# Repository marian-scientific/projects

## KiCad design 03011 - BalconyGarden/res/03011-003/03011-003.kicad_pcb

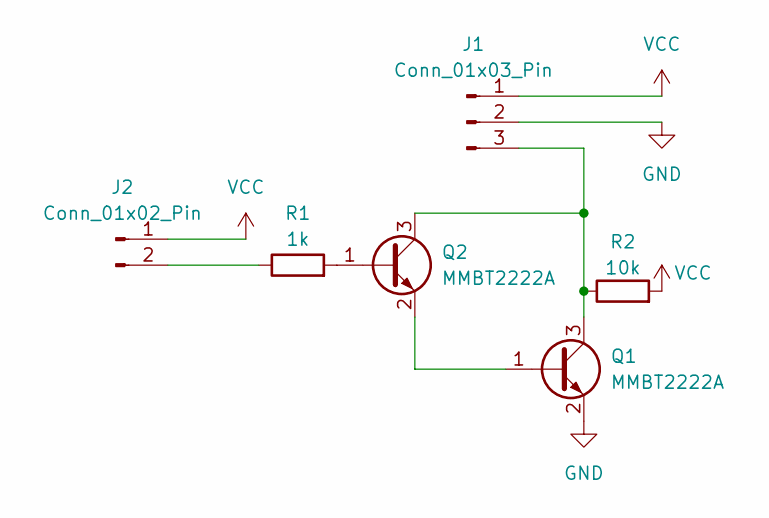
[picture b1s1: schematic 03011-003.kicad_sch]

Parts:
J1: Conn_01x03_Pin; PinHeader_1x03_P2.54mm_Vertical
J2: Conn_01x02_Pin; PinHeader_1x02_P2.54mm_Vertical
Q1, Q2: MMBT2222A; SOT-23
R1: 1k; R_1206_3216Metric
R2: 10k; R_1206_3216Metric

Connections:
GND: J1.2, Q1.2 (E)
unnamed: J1.3, Q1.3 (C), Q2.3 (C), R2.1
unnamed: J2.2, R1.1
unnamed: Q1.1 (B), Q2.2 (E)
unnamed: Q2.1 (B), R1.2
VCC: J1.1, J2.1, R2.2

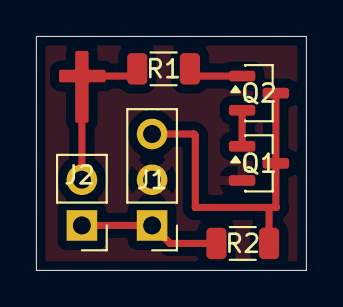
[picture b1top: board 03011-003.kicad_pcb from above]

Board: 2 copper layers, 15.0 x 13.0 mm, 6 parts (0 on the bottom side), 6 nets.

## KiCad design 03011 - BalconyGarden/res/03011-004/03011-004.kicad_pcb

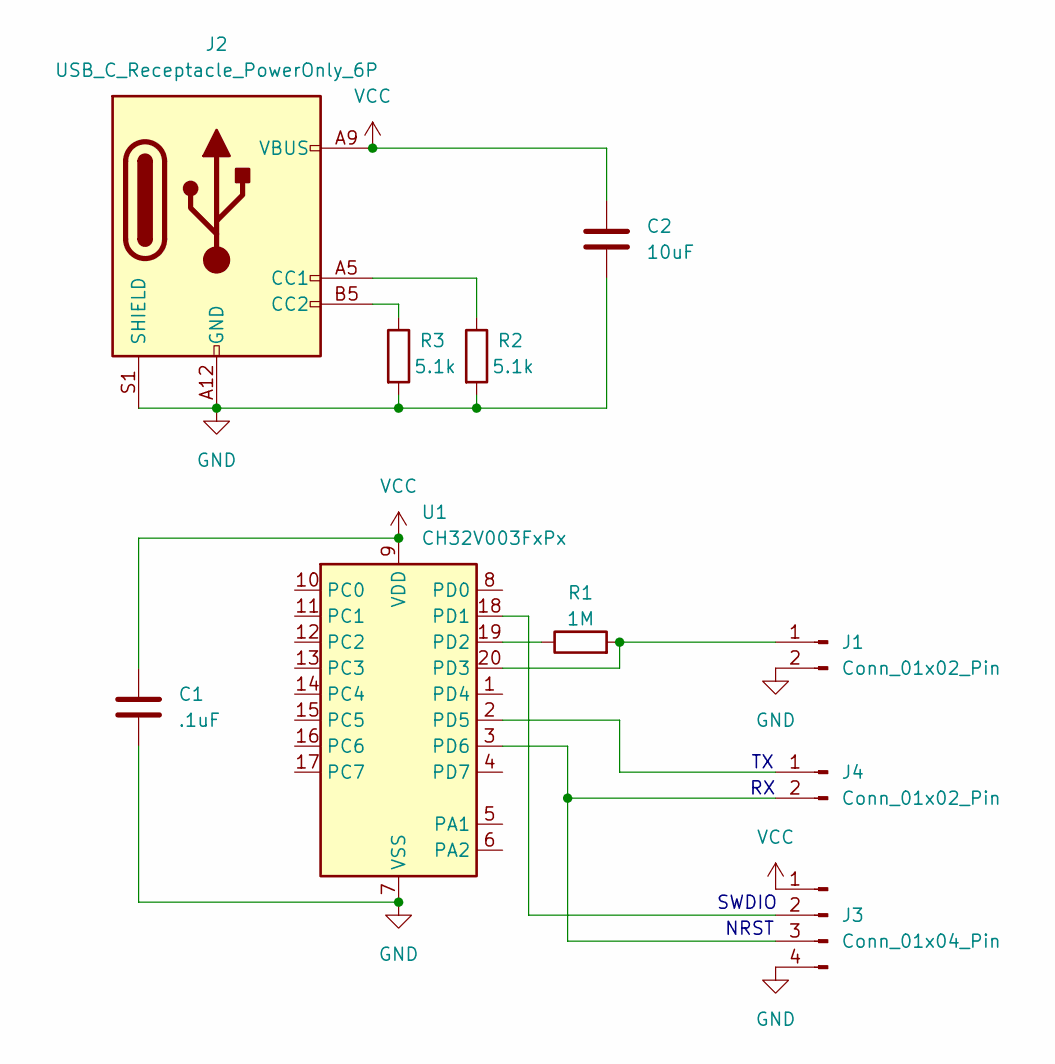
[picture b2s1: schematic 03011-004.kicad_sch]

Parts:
C1: .1uF; C_1206_3216Metric
C2: 10uF; C_1206_3216Metric
J1, J4: Conn_01x02_Pin; PinHeader_1x02_P2.54mm_Vertical
J2: USB_C_Receptacle_PowerOnly_6P; USB_C_Receptacle_GCT_USB4125-xx-x_6P_TopMnt_Horizontal
J3: Conn_01x04_Pin; PinHeader_1x04_P2.54mm_Vertical
R1: 1M; R_1206_3216Metric
R2, R3: 5.1k; R_1206_3216Metric
U1: CH32V003FxPx; TSSOP-20_4.4x6.5mm_P0.65mm

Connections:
GND: C1.2, C2.2, J1.2, J2.A12 (GND), J2.B12 (GND), J2.S1 (SHIELD), J3.4, R2.2, R3.2, U1.7 (VSS)
unnamed: J1.1, R1.2, U1.20 (PD3)
unnamed: J2.A5 (CC1), R2.1
unnamed: J2.B5 (CC2), R3.1
unnamed: J3.2, U1.18 (PD1)
unnamed: J3.3, J4.2, U1.3 (PD6)
unnamed: J4.1, U1.2 (PD5)
unnamed: R1.1, U1.19 (PD2)
VCC: C1.1, C2.1, J2.A9 (VBUS), J2.B9 (VBUS), J3.1, U1.9 (VDD)

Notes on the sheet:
SWDIO
NRST

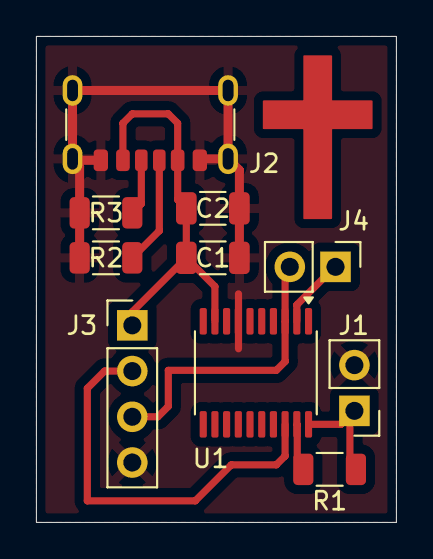
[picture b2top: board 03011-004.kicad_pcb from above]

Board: 2 copper layers, 20.0 x 27.0 mm, 10 parts (0 on the bottom side), 9 nets.

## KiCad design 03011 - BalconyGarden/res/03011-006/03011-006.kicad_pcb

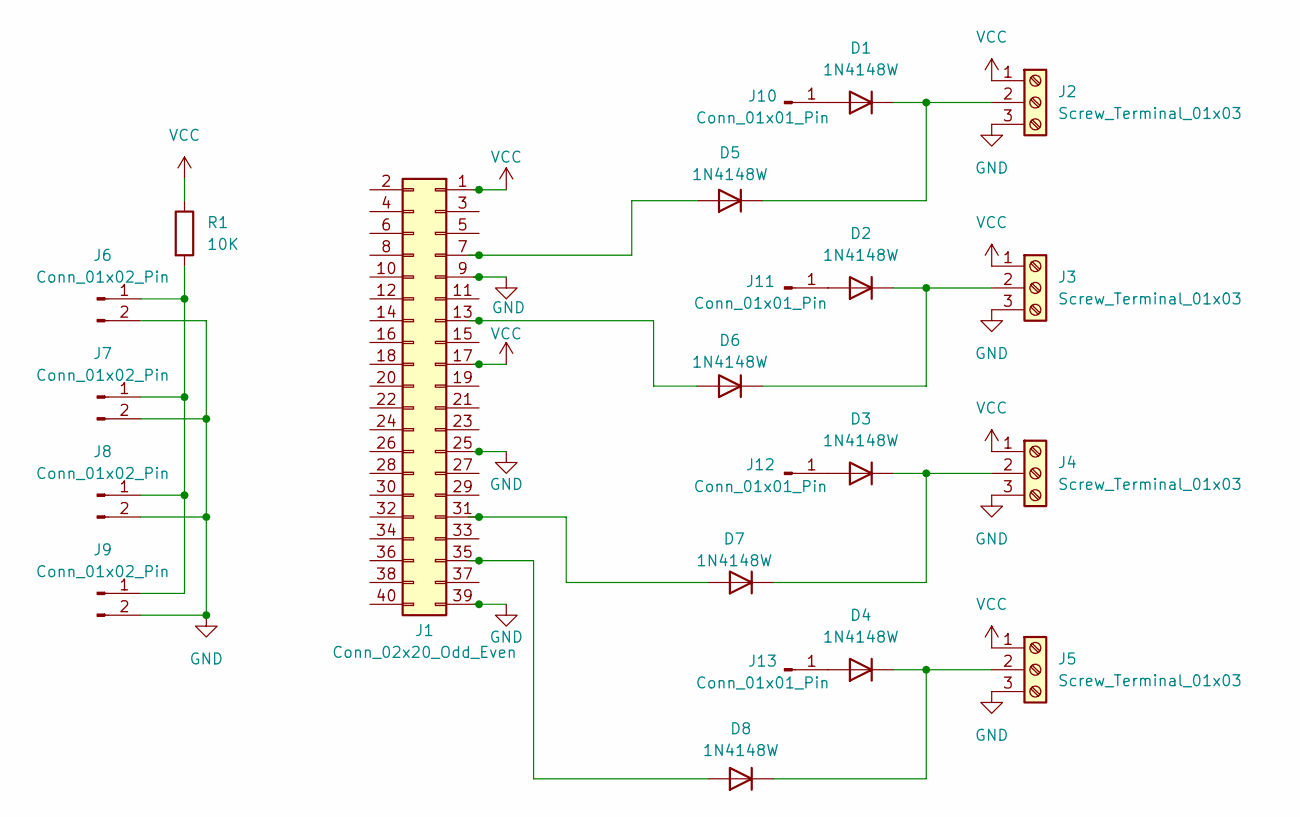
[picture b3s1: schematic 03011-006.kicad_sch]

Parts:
D1, D2, D3, D4, D5, D6, D7, D8: 1N4148W; D_SOD-123
J1: Conn_02x20_Odd_Even; PinSocket_2x20_P2.54mm_Vertical
J2, J3, J4, J5: Screw_Terminal_01x03; TerminalBlock_TE_282834-3_1x03_P2.54mm_Horizontal
J6, J7, J8, J9: Conn_01x02_Pin; PinHeader_1x02_P2.54mm_Vertical
J10, J11, J12, J13: Conn_01x01_Pin; PinHeader_1x01_P2.54mm_Vertical
R1: 10K; R_1206_3216Metric

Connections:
GND: J1.9, J1.25, J1.39, J2.3, J3.3, J4.3, J5.3, J6.2, J7.2, J8.2, J9.2
unnamed: D1.2 (A), J10.1
unnamed: D1.1 (K), D5.1 (K), J2.2
unnamed: D2.2 (A), J11.1
unnamed: D2.1 (K), D6.1 (K), J3.2
unnamed: D3.2 (A), J12.1
unnamed: D3.1 (K), D7.1 (K), J4.2
unnamed: D4.2 (A), J13.1
unnamed: D4.1 (K), D8.1 (K), J5.2
unnamed: D5.2 (A), J1.7
unnamed: D6.2 (A), J1.13
unnamed: D7.2 (A), J1.31
unnamed: D8.2 (A), J1.35
unnamed: J6.1, J7.1, J8.1, J9.1, R1.2
VCC: J1.1, J1.17, J2.1, J3.1, J4.1, J5.1, R1.1

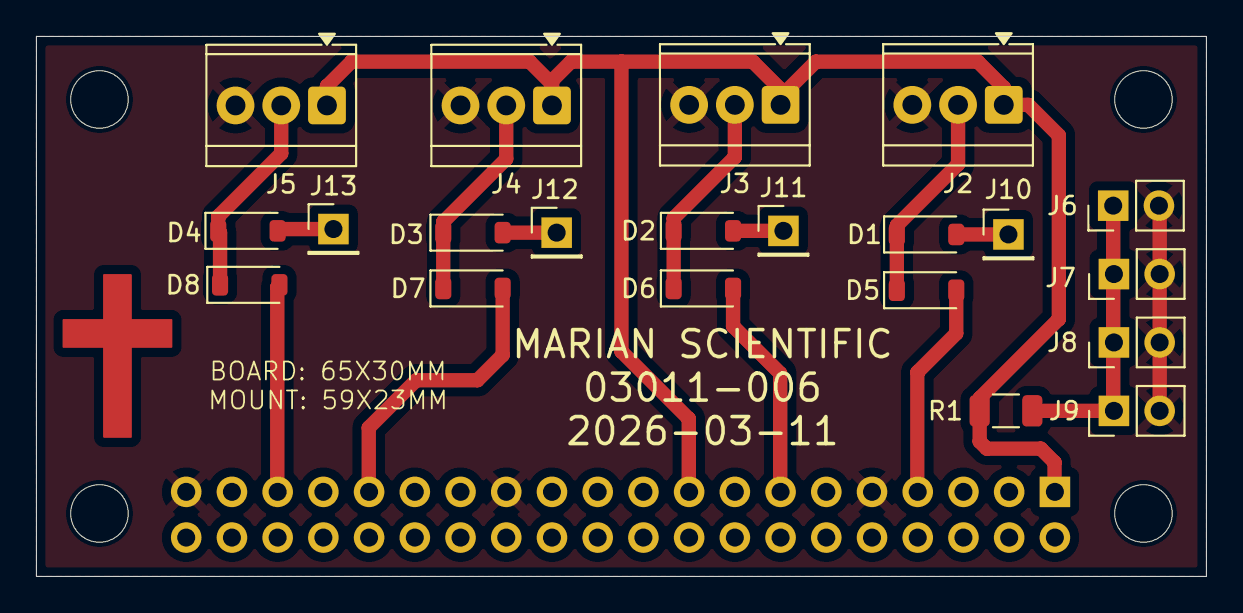
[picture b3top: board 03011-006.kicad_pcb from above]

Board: 2 copper layers, 65.0 x 30.0 mm, 22 parts (1 on the bottom side), 15 nets.

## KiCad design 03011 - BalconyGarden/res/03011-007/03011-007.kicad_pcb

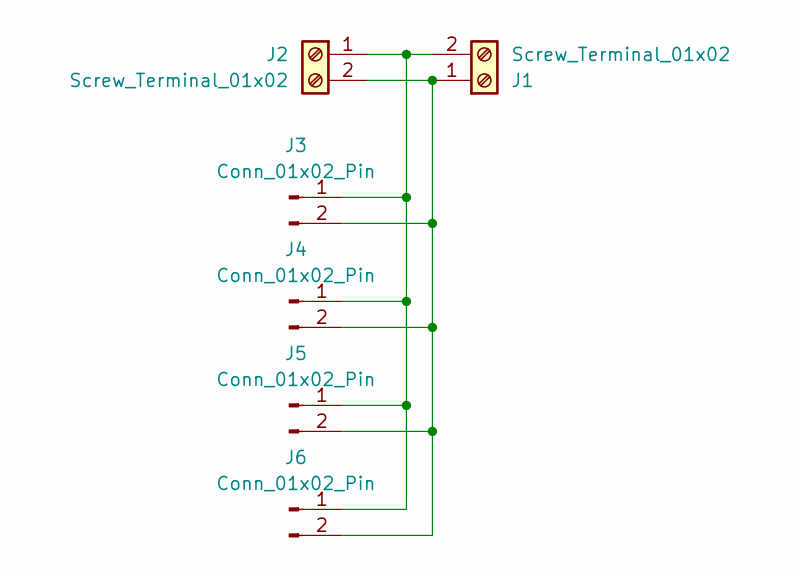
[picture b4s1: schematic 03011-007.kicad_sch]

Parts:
J1, J2: Screw_Terminal_01x02; TerminalBlock_TE_282834-2_1x02_P2.54mm_Horizontal
J3, J4, J5, J6: Conn_01x02_Pin; PinHeader_1x02_P2.54mm_Vertical

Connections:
unnamed: J1.1, J2.2, J3.2, J4.2, J5.2, J6.2
unnamed: J1.2, J2.1, J3.1, J4.1, J5.1, J6.1

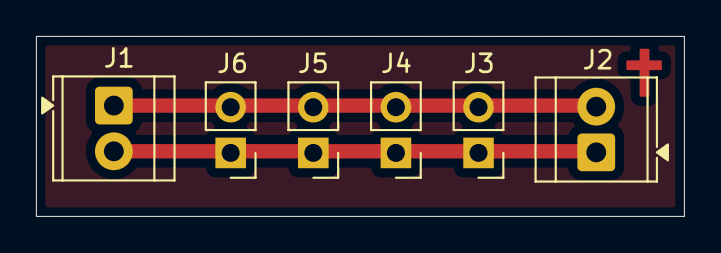
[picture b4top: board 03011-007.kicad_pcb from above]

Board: 2 copper layers, 36.0 x 10.0 mm, 6 parts (0 on the bottom side), 2 nets.

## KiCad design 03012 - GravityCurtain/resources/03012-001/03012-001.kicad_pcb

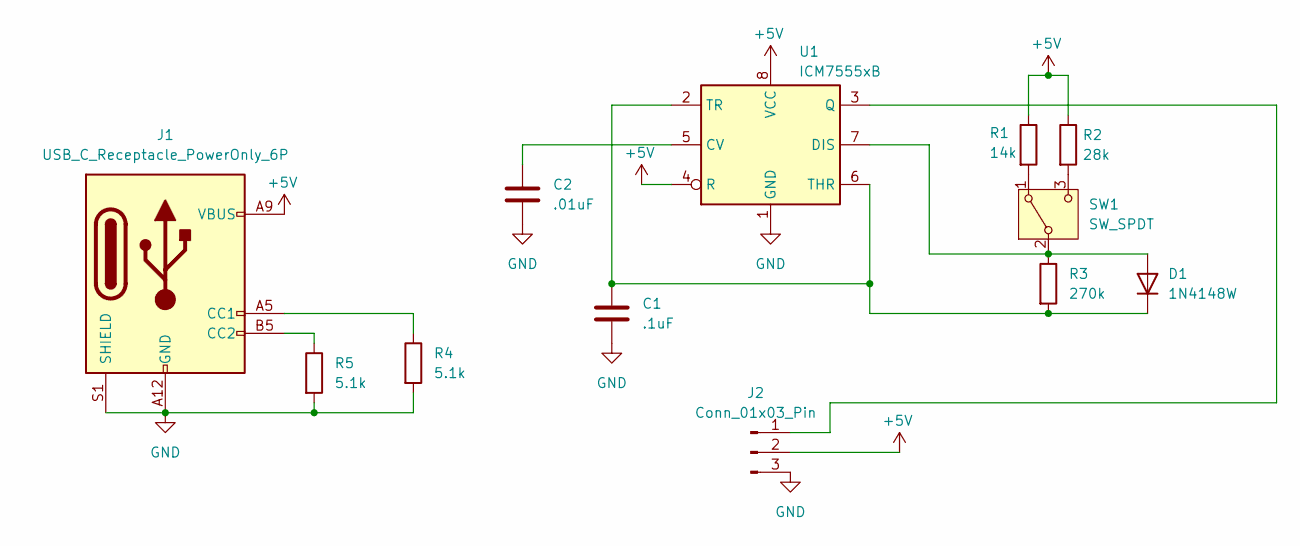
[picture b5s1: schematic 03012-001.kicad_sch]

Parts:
C1: .1uF; C_1206_3216Metric
C2: .01uF; C_1206_3216Metric
D1: 1N4148W; D_SOD-123
J1: USB_C_Receptacle_PowerOnly_6P; USB_C_Receptacle_GCT_USB4125-xx-x_6P_TopMnt_Horizontal
J2: Conn_01x03_Pin; PinHeader_1x03_P2.54mm_Vertical
R1: 14k; R_1206_3216Metric
R2: 28k; R_1206_3216Metric
R3: 270k; R_1206_3216Metric
R4, R5: 5.1k; R_1206_3216Metric
SW1: SW_SPDT; SW_Slide-03_Wuerth-WS-SLTV_10x2.5x6.4_P2.54mm
U1: ICM7555xB; SOIC-8_3.9x4.9mm_P1.27mm

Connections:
+5V: J1.A9 (VBUS), J1.B9 (VBUS), J2.2, R1.1, R2.1, U1.4 (R), U1.8 (VCC)
GND: C1.2, C2.2, J1.A12 (GND), J1.B12 (GND), J1.S1 (SHIELD), J2.3, R4.2, R5.2, U1.1 (GND)
unnamed: D1.2 (A), R3.1, SW1.2 (B), U1.7 (DIS)
unnamed: C1.1, D1.1 (K), R3.2, U1.2 (TR), U1.6 (THR)
unnamed: J1.A5 (CC1), R4.1
unnamed: J1.B5 (CC2), R5.1
unnamed: J2.1, U1.3 (Q)
unnamed: R1.2, SW1.1 (A)
unnamed: R2.2, SW1.3 (C)
unnamed: C2.1, U1.5 (CV)

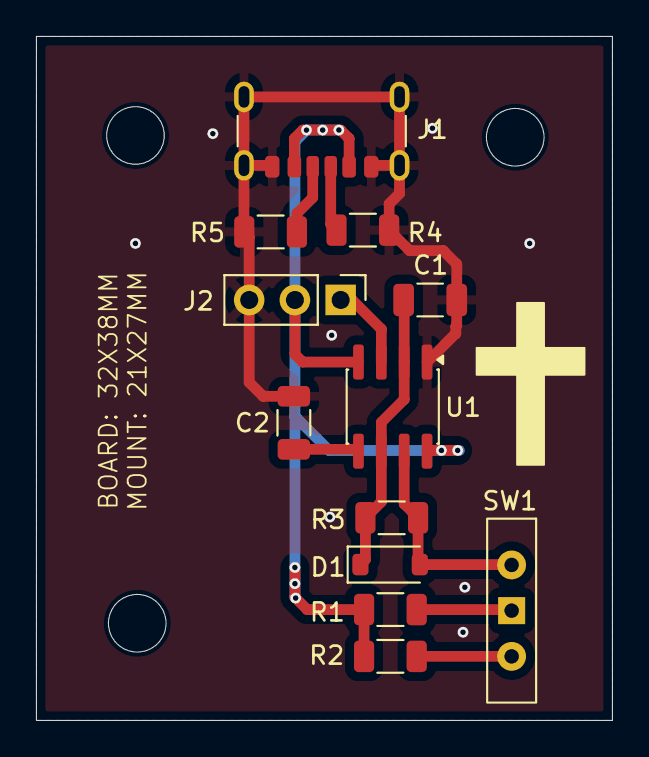
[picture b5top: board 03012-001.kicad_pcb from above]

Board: 2 copper layers, 32.0 x 38.0 mm, 12 parts (0 on the bottom side), 10 nets.

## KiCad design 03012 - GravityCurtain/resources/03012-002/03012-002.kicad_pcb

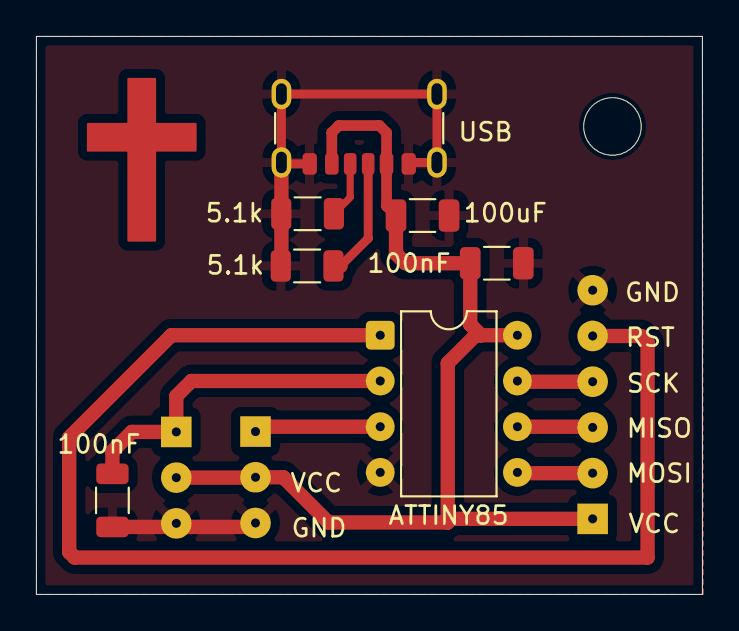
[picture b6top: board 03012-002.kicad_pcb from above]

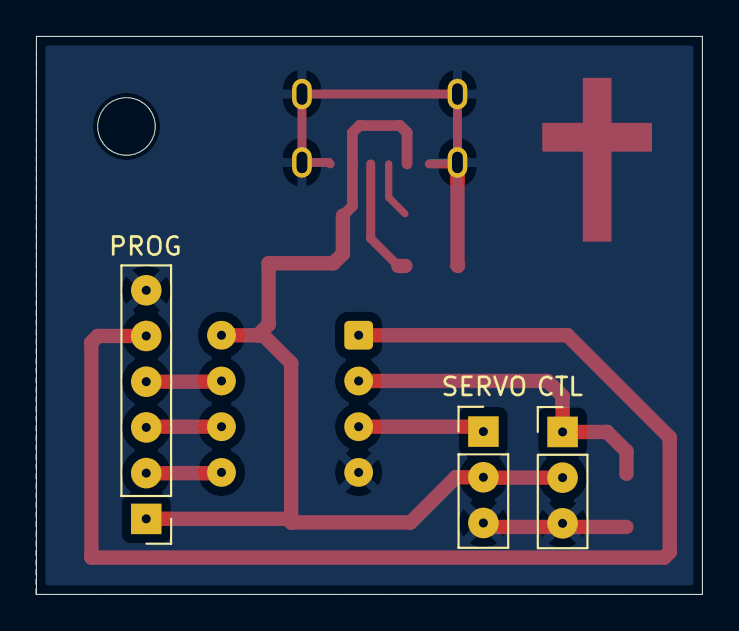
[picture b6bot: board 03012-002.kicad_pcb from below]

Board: 2 copper layers, 37.0 x 31.0 mm, 10 parts (3 on the bottom side), 10 nets.

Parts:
5.1k: 5.1k; R_1206_3216Metric
100nF, 100nF#2: 100nF; C_1206_3216Metric
100uF: 100uF; C_1206_3216Metric
ATTINY85: ATtiny85-20P; DIP-8_W7.62mm
CTL: Conn_01x03_Pin; PinHeader_1x03_P2.54mm_Vertical
PROG: Conn_01x06_Pin; PinHeader_1x06_P2.54mm_Vertical
R2: 5.1k; R_1206_3216Metric
SERVO: Conn_01x03_Pin; PinHeader_1x03_P2.54mm_Vertical
USB: USB_C_Receptacle_PowerOnly_6P; USB_C_Receptacle_GCT_USB4125-xx-x_6P_TopMnt_Horizontal

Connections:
GND: 5.1k.2, 100nF.2, 100nF#2.2, 100uF.2, ATTINY85.4 (GND), CTL.3, PROG.6, R2.2, SERVO.3, USB.A12 (GND), USB.B12 (GND), USB.S1 (SHIELD)
unnamed: R2.1, USB.A5 (CC1)
unnamed: 5.1k.1, USB.B5 (CC2)
unnamed: ATTINY85.5 (AREF/PB0), PROG.2
unnamed: ATTINY85.6 (PB1), PROG.3
unnamed: ATTINY85.7 (PB2), PROG.4
unnamed: ATTINY85.1 (~RESET/PB5), PROG.5
unnamed: ATTINY85.3 (XTAL2/PB4), SERVO.1
unnamed: 100nF#2.1, ATTINY85.2 (XTAL1/PB3), CTL.1
VCC: 100nF.1, 100uF.1, ATTINY85.8 (VCC), CTL.2, PROG.1, SERVO.2, USB.A9 (VBUS), USB.B9 (VBUS)

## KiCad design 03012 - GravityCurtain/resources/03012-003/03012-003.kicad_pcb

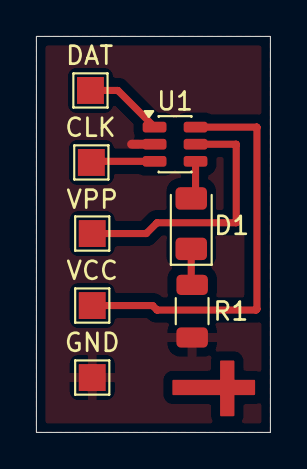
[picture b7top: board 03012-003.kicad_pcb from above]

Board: 2 copper layers, 13.0 x 22.0 mm, 8 parts (0 on the bottom side), 7 nets.

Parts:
D1: LED; LED_1206_3216Metric
R1: 330; R_1206_3216Metric
TP1: DAT; TestPoint_Pad_1.5x1.5mm
TP2: GND; TestPoint_Pad_1.5x1.5mm
TP3: CLK; TestPoint_Pad_1.5x1.5mm
TP4: VCC; TestPoint_Pad_1.5x1.5mm
TP5: VPP; TestPoint_Pad_1.5x1.5mm
U1: PIC10F320-IOT; SOT-23-6

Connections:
GND: R1.2, TP2.1, U1.2 (VSS)
unnamed: D1.2 (A), U1.4 (RA2)
unnamed: D1.1 (K), R1.1
unnamed: TP1.1, U1.1 (RA0)
unnamed: TP3.1, U1.3 (RA1)
unnamed: TP4.1, U1.6 (RA3)
VCC: TP5.1, U1.5 (VDD)
